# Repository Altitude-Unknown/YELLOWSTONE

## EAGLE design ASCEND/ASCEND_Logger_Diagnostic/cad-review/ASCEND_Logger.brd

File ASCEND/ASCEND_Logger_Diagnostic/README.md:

# ASCEND Logger v11 bench diagnostic

This smaller SAMD21 logger has GPS, a barometer and SD, without a LoRa radio.
Optional humidity and PM sensors are not required by this diagnostic.

Connected board on 2026-10-26: `/dev/cu.usbmodem1201`, detected as
`AltitudeUnknown:samd:altitude_yellowstone_m0`. This package uses the
`feather_m0_express` variant. Schematic matches SDA PA22, SCL PA23,
SD CS D10/PA18, MOSI PB10, SCK PB11, MISO PA12.

```sh
arduino-cli compile --fqbn AltitudeUnknown:samd:altitude_yellowstone_m0 ASCEND/ASCEND_Logger_Diagnostic
arduino-cli upload -p /dev/cu.usbmodem1201 --fqbn AltitudeUnknown:samd:altitude_yellowstone_m0 ASCEND/ASCEND_Logger_Diagnostic
```

Open USB serial at 115200 to start. The diagnostic scans I2C, checks the
barometer PROM CRC and conversion data, then polls fresh GPS NAV-PVT messages
and barometer readings every two seconds. It does not change persistent GPS
configuration, transmit radio packets or write SD files.

## Initial results — October 26, 2026

- USB upload and flash verification passed for both sketches. MCU heartbeat
  continues during GPS/barometer testing.
- Standalone `Yellowstone_SD_Arduino_Test` passed: initialization, appending
  `testing 1, 2, 3.` to `test.txt`, closing, reopening and reading back.
  User confirmed an SD card is inserted. No formatting was performed.
- I2C SDA/SCL HIGH; only addresses 0x42 and 0x76 found.
- GPS 0x42: UBX communication and repeated fresh NAV-PVT messages passed.
  Initial capture: fix_type=0, fix_ok=0, satellites=0, date_valid=0,
  time_valid=0. Satellite reception/navigation fix not yet verified.
- Barometer 0x76: PROM `00BC BC29 C5A5 6E1A 6A4D 7C34 6653 48E9`;
  stored CRC=9, calculated CRC=9. Repeated nonzero ADC conversions passed.
- User identified the fitted part as MS5607, but this requires rechecking:
  D1=7999760, D2=8530462 gives approximately 1700.47 hPa / 32.20 C with
  MS5607 compensation. Pressure is implausible for ambient conditions.
  MS5611 compensation would give approximately 850.24 hPa. This is evidence
  of a possible model mismatch, not proof of component identity or accuracy.
  Do not pass absolute pressure measurement or silently change the model.
- No humidity/PM devices were detected or tested. No LoRa is fitted/tested.

The sketch is bench firmware, not a deployment-ready standalone logger.

## Component identification resolved

User corrected the fitted barometer to **MS5611** after reviewing the pressure
discrepancy. Diagnostic now uses MS5611 compensation. Schematic U1 value still
mentions MS5607; update that BOM/value in the CAD source to avoid future confusion.
User moved the powered board to a clear sky view for the reception test.

## Latest result after correction and outdoor test

- MS5611: steady pressure approximately 849.5–849.9 hPa, with die temperature
  falling from approximately 28 C indoors to 9.4 C outside. Basic measurement
  function passes; no calibrated reference comparison was performed.
- User confirmed W3011 antenna fitted and subsequently moved fully outdoors.
- GPS, GPS L1 C/A, Galileo and GLONASS configuration keys all read enabled (1).
  These were read only; no GNSS settings were written.
- Outdoor NAV-PVT still has no fix, zero satellites used and invalid UTC.
  NAV-SAT has no positive-C/N0 signals; occasional listed satellites do not
  establish reception. Latest captures list zero satellites.
- MON-RF block 0: noise=94, AGC=5616, jamming-state=0, indicator=25–30.
  State 0 means unknown/disabled, not proof of no interference. These values
  do not identify a particular fault.
- GPS digital communication passes; reception/navigation has NOT passed.
  Next inspect antenna keepout/placement, feed trace, C10, antenna/module
  solder joints and RF ground/layout. Need PCB layout or photos for review.
- Final installed sketch: ASCEND_Logger_Diagnostic, 54396 bytes compiled;
  upload and flash verification passed. Serial 115200. SD is deselected;
  standalone SD test already passed. This is not production logging firmware.

W3011 manufacturer layout reference:
https://productfinder.pulseeng.com/doc_type/WEB301/doc_num/W3011/doc_part/W3011.pdf
Ground clearance and application-dependent matching cannot be checked from
the schematic alone.

## Assembly photo and layout screenshot review

User supplied `PXL_20261026_201813004.MACRO_FOCUS.jpg` and a Fusion layout
screenshot. W3011 is fitted. Its manufacturer drawing states it is symmetrical:
either terminal can be feed/ground, so a 180-degree rotation is not itself an
assembly error. The layout screenshot shows a clearance region, but does not
provide dimensions or independently verify every copper layer. No solder
bridge/open can be conclusively diagnosed from the photo. RF_IN pad 11 and
adjacent grounds 10/12 need close physical inspection; verify continuity of
the RF feed and actual fitted C10 value (schematic 2.2 pF). Asked user to
confirm C10. Do not infer capacitor value from its unmarked appearance.

Repeat serial check after image submission still no fix or positive-C/N0
signals. GPS communication and barometer continue working (~850.2 hPa).

## GPS reception recovered — later October 26

User reported signal and requested another check. Read-only capture on
`/dev/cu.usbmodem1201` at 115200 now shows repeated changing latitude,
longitude and altitude outputs, with SIV 4–6 and altitude about 1490–1493 m.
Exact coordinates omitted from these notes. GPS satellite reception and
position output are now demonstrated. This different serial format indicates
the running firmware changed outside the assistant's last upload; do not
claim ASCEND_Logger_Diagnostic remains installed. This capture does not expose
fix_type/fix_ok/UTC validity, so those flags were not independently verified.
No firmware was flashed in this recheck. Hardware modifications (including
V_BCKP jumper) were not confirmed; do not attribute recovery to any correction.
Earlier no-reception observations are historical, not the current status.

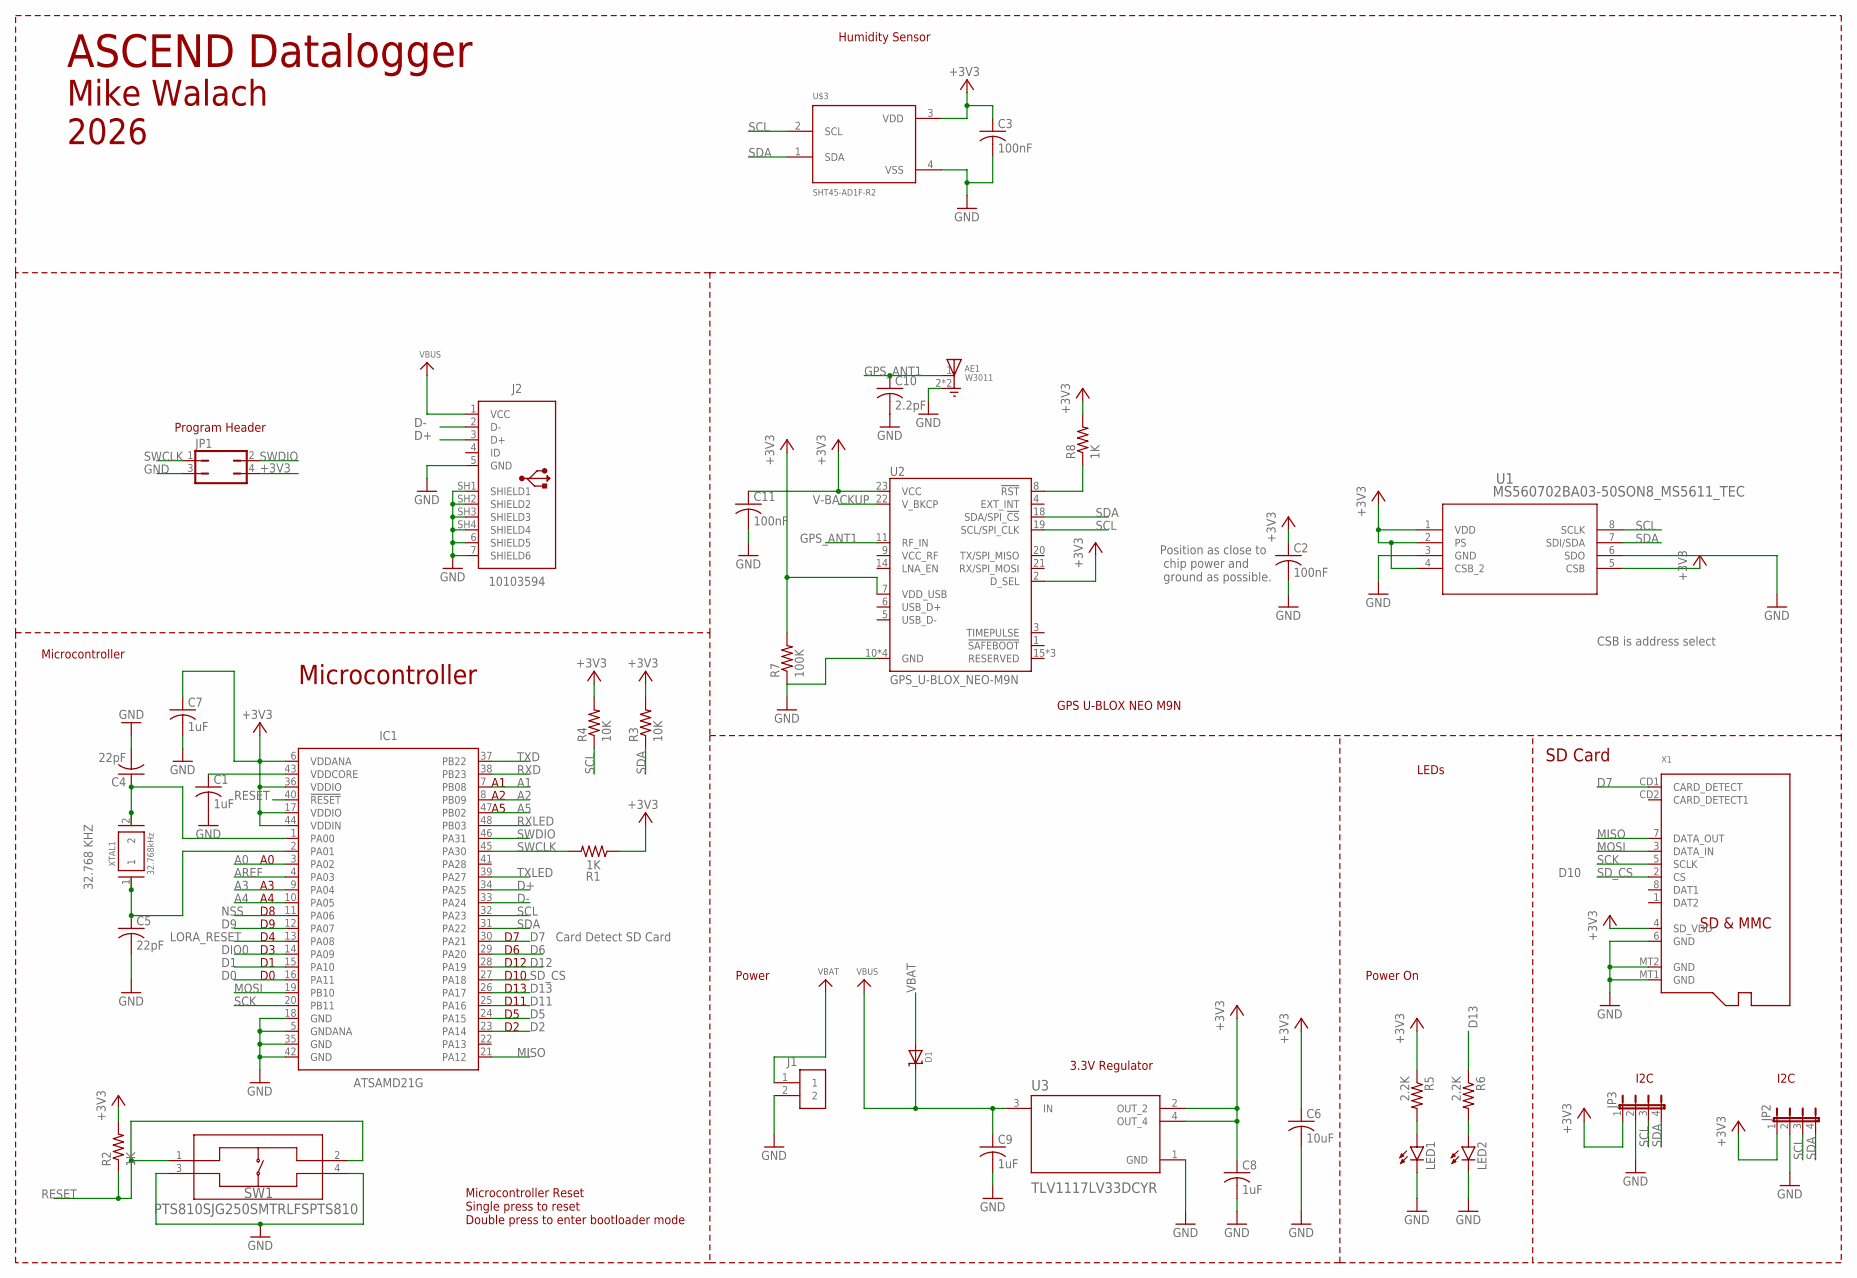
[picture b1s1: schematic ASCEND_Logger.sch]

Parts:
AE1: W3011; XDCR_W3011
C1, C7, C8, C9: 1uF; C0805
C2, C3, C11: 100nF; C0805
C4, C5: 22pF; C0805
C6: 10uF; C0805
C10: 2.2pF; C0805
D1: MICROBUILDER_DIODE-SCHOTTKYSOD-123; MICROBUILDER_SOD-123
IC1: ATSAMD21G; QFP50P900X900X120-48
J1: S2B-PH-K-S(LF)(SN)
J2: 10103594
JP1: JP2Q
JP2, JP3: JP4E; JP4
LED1, LED2: LEDSML0805; SML0805
R1, R2, R8: 1K; R0805
R3, R4: 10K; R0805
R5, R6: 2.2K; R0805
R7: 100K; R0805
SW1: PTS810SJG250SMTRLFSPTS810; PTS810
U1: MS560702BA03-50SON8_MS5611_TEC; SON8_MS5611_TEC
U2: GPS_U-BLOX_NEO-M9N; GPS_NEO-M9N
U3: TLV1117LV33DCYR; VREG_TLV1117LV33DCYR
U$3: SHT45-AD1F-R2; SHT4X_HAND_SOLDER
X1: MICROBUILDER_MICROSD
XTAL1: 32.768kHz; XTAL_ABS07-32.768KHZ-T

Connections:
+3V3: C2.1, C3.1, C6.1, C7.1, C8.1, C11.1, IC1.6 (VDDANA), IC1.17 (VDDIO), IC1.36 (VDDIO), IC1.44 (VDDIN), JP1.4, JP2.1, JP3.1, R1.1, R2.2, R3.2, R4.2, R5.1, R7.2, R8.2, U1.1 (VDD), U1.2 (PS), U1.4 (CSB_2), U1.5 (CSB), U2.2 (D_SEL), U2.7 (VDD_USB), U2.23 (VCC), U3.2 (OUT_2), U3.4 (OUT_4), U$3.3 (VDD), X1.4 (SD_VDD)
A0: IC1.3 (PA02)
A1: IC1.7 (PB08)
A2: IC1.8 (PB09)
A3: IC1.9 (PA04)
A4: IC1.10 (PA05)
A5: IC1.47 (PB02)
AREF: IC1.4 (PA03)
D0: IC1.16 (PA11)
D1: IC1.15 (PA10)
D2: IC1.23 (PA14)
D5: IC1.24 (PA15)
D6: IC1.29 (PA20)
D7: IC1.30 (PA21), X1.CD1 (CARD_DETECT)
D9: IC1.12 (PA07)
D11: IC1.25 (PA16)
D12: IC1.28 (PA19)
D13: IC1.26 (PA17), R6.1
D+: IC1.34 (PA25), J2.3 (D+)
D-: IC1.33 (PA24), J2.2 (D-)
DIO0: IC1.14 (PA09)
GND: AE1.2 (GND), AE1.3 (GND), C1.2, C2.2, C3.2, C4.2, C5.2, C6.2, C7.2, C8.2, C9.2, C10.2, C11.2, IC1.5 (GNDANA), IC1.18 (GND), IC1.35 (GND), IC1.42 (GND), J1.2, J2.5 (GND), J2.6 (SHIELD5), J2.7 (SHIELD6), J2.SH1 (SHIELD1), J2.SH2 (SHIELD2), J2.SH3 (SHIELD3), J2.SH4 (SHIELD4), JP1.3, JP2.2, JP3.2, LED1.C, LED2.C, R7.1, SW1.3, SW1.4, U1.3 (GND), U1.6 (SDO), U2.10 (GND), U2.12 (GND), U2.13 (GND), U2.24 (GND), U3.1 (GND), U$3.4 (VSS), X1.6 (GND), X1.MT1 (GND), X1.MT2 (GND)
GPS_ANT1: AE1.1 (FEED), C10.1, U2.11 (RF_IN)
LORA_RESET: IC1.13 (PA08)
MISO: IC1.21 (PA12), X1.7 (DATA_OUT)
MOSI: IC1.19 (PB10), X1.3 (DATA_IN)
unnamed: C1.1, IC1.43 (VDDCORE)
unnamed: LED2.A, R6.2
unnamed: R8.1, U2.8 (!RST)
unnamed: C5.1, IC1.2 (PA01), XTAL1.1
unnamed: C4.1, IC1.1 (PA00), XTAL1.2
unnamed: LED1.A, R5.2
NSS: IC1.11 (PA06)
RESET: IC1.40 (!RESET), R2.1, SW1.1, SW1.2
RXD: IC1.38 (PB23)
RXLED: IC1.48 (PB03)
SCK: IC1.20 (PB11), X1.5 (SCLK)
SCL: IC1.32 (PA23), JP2.3, JP3.3, R4.1, U1.8 (SCLK), U2.19 (SCL/SPI_CLK), U$3.2 (SCL)
SDA: IC1.31 (PA22), JP2.4, JP3.4, R3.1, U1.7 (SDI/SDA), U2.18 (SDA/SPI_!CS!), U$3.1 (SDA)
SD_CS: IC1.27 (PA18), X1.2 (CS)
SWCLK: IC1.45 (PA30), JP1.1, R1.2
SWDIO: IC1.46 (PA31), JP1.2
TXD: IC1.37 (PB22)
TXLED: IC1.39 (PA27)
V-BACKUP: U2.22 (V_BKCP)
VBAT: D1.A, J1.1
VBUS: C9.1, D1.C, J2.1 (VCC), U3.3 (IN)

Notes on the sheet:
Power
SD Card
Microcontroller
32.768 KHZ
Mike Walach 2026
D10
LEDs
Power On
Microcontroller Reset Single press to reset Double press to enter bootloader mode
ASCEND Datalogger
D13
D11
D12
I2C
Card Detect SD Card
GPS U-BLOX NEO M9N
CSB is address select
Position as close to chip power and ground as possible.
Program Header
3.3V Regulator
Humidity Sensor

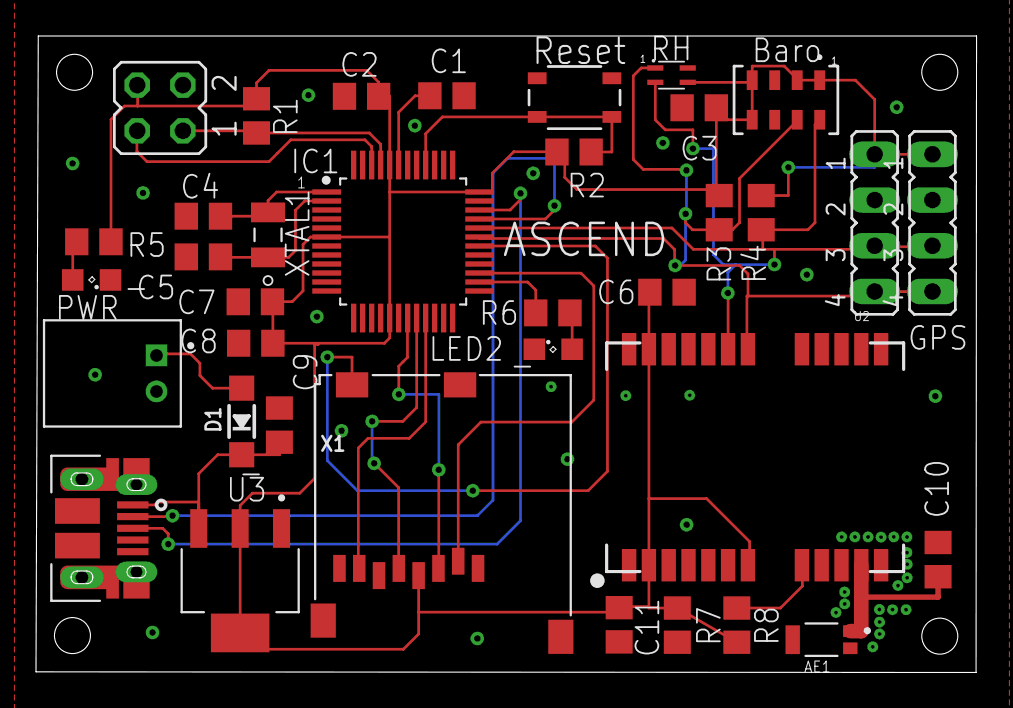
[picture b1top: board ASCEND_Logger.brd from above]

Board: 2 copper layers, 52.3 x 35.4 mm, 36 parts (0 on the bottom side), 24 nets.

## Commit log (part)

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2026-06-18 Initial Yellowstone project split
2026-06-19 Add custom YELLOWSTONE SAMD21 bootloader
2026-06-20 Add YELLOWSTONE PCB schematic
2026-06-20 Document YELLOWSTONE PCB schematic
2026-06-25 Set up Yellowstone release workflow in dedicated repo
2026-06-25 Fix Yellowstone release workflow signing and artifact paths
2026-06-30 Update Yellowstone ground telemetry v3 support

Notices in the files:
parts and their libraries:
COPYRIGHT: Copyright (C) 2025 Ultra Librarian. All rights reserved.
COPYRIGHT: Copyright (C) 2024 Ultra Librarian. All rights reserved.
